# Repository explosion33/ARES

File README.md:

# ARES
Controls and Electronics Repository for SARP's Autonomous Recovery Experimental System (ARES).

## Directory / Ownership

[CC1200 Radio Board / ARES RF Board](https://github.com/stars/explosion33/lists/cc1200-radio-project) | Ethan Armstrong
<br/>
ARES RF board group: KiCad files, Firmware, supporting software

*/CAD*
<br/>
ARES PCB CAD

*/HBridgeTest*
<br/>
HBridge breadboard sample / control code

*/Hardware/Flight_Computer* | Jimmy Fowler
<br/>
ARES Flight Computer PCB Kicad Files

*/Hardware/motor_control_design* | Oliver Buehrer, Ethan Armstrong
<br/>
ARES Actuation (Motor Control) / Power Supply Board Kicad files

*/Renders*
<br/>
ARES PCB Renders

*/Software/Simulation* | Jimmy Fowler
<br/>
ARES simulation code

*/Testbed*
<br/>
ARES Testbed firmware

*/UI*
<br/>
ARES Ground Station UI

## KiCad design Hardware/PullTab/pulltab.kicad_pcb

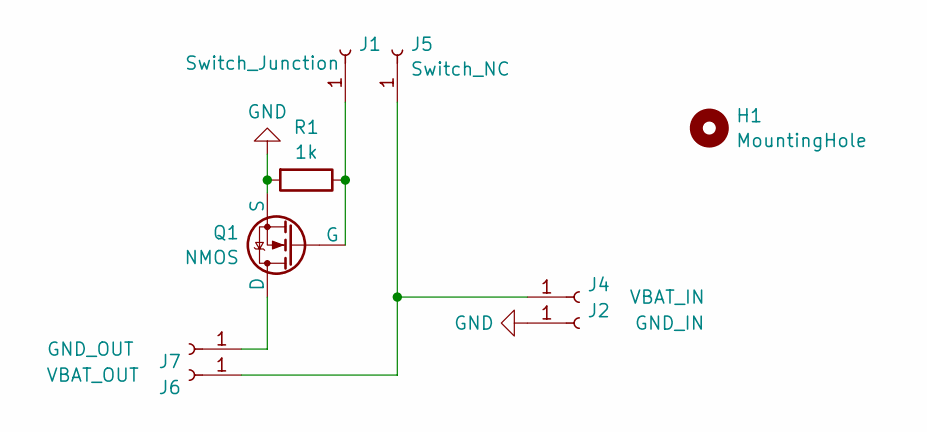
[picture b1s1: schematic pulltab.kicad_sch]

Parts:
H1: MountingHole; MountingHole_2.2mm_M2
J1: Switch_Junction; TestPoint_Pad_2.5x2.5mm
J2: GND_IN; TestPoint_Pad_4.0x4.0mm
J4: VBAT_IN; TestPoint_Pad_4.0x4.0mm
J5: Switch_NC; TestPoint_Pad_2.5x2.5mm
J6: VBAT_OUT; TestPoint_Pad_4.0x4.0mm
J7: GND_OUT; TestPoint_Pad_4.0x4.0mm
Q1: NMOS; TO-220-3_Horizontal_TabDown
R1: 1k; R_Axial_DIN0204_L3.6mm_D1.6mm_P5.08mm_Horizontal

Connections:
GND: J2.1, Q1.3 (S), R1.2
unnamed: J1.1, Q1.1 (G), R1.1
unnamed: J4.1, J5.1, J6.1
unnamed: J7.1, Q1.2 (D)

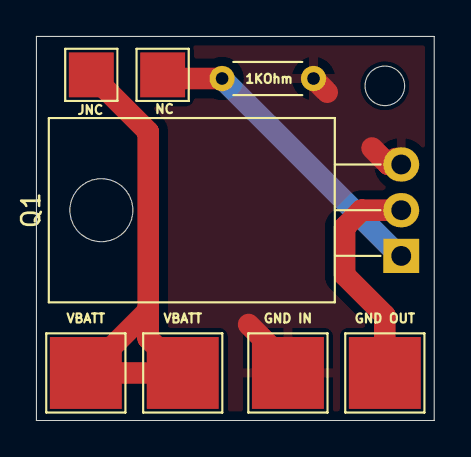
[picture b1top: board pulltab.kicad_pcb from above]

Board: 2 copper layers, 22.1 x 21.3 mm, 9 parts (0 on the bottom side), 4 nets.

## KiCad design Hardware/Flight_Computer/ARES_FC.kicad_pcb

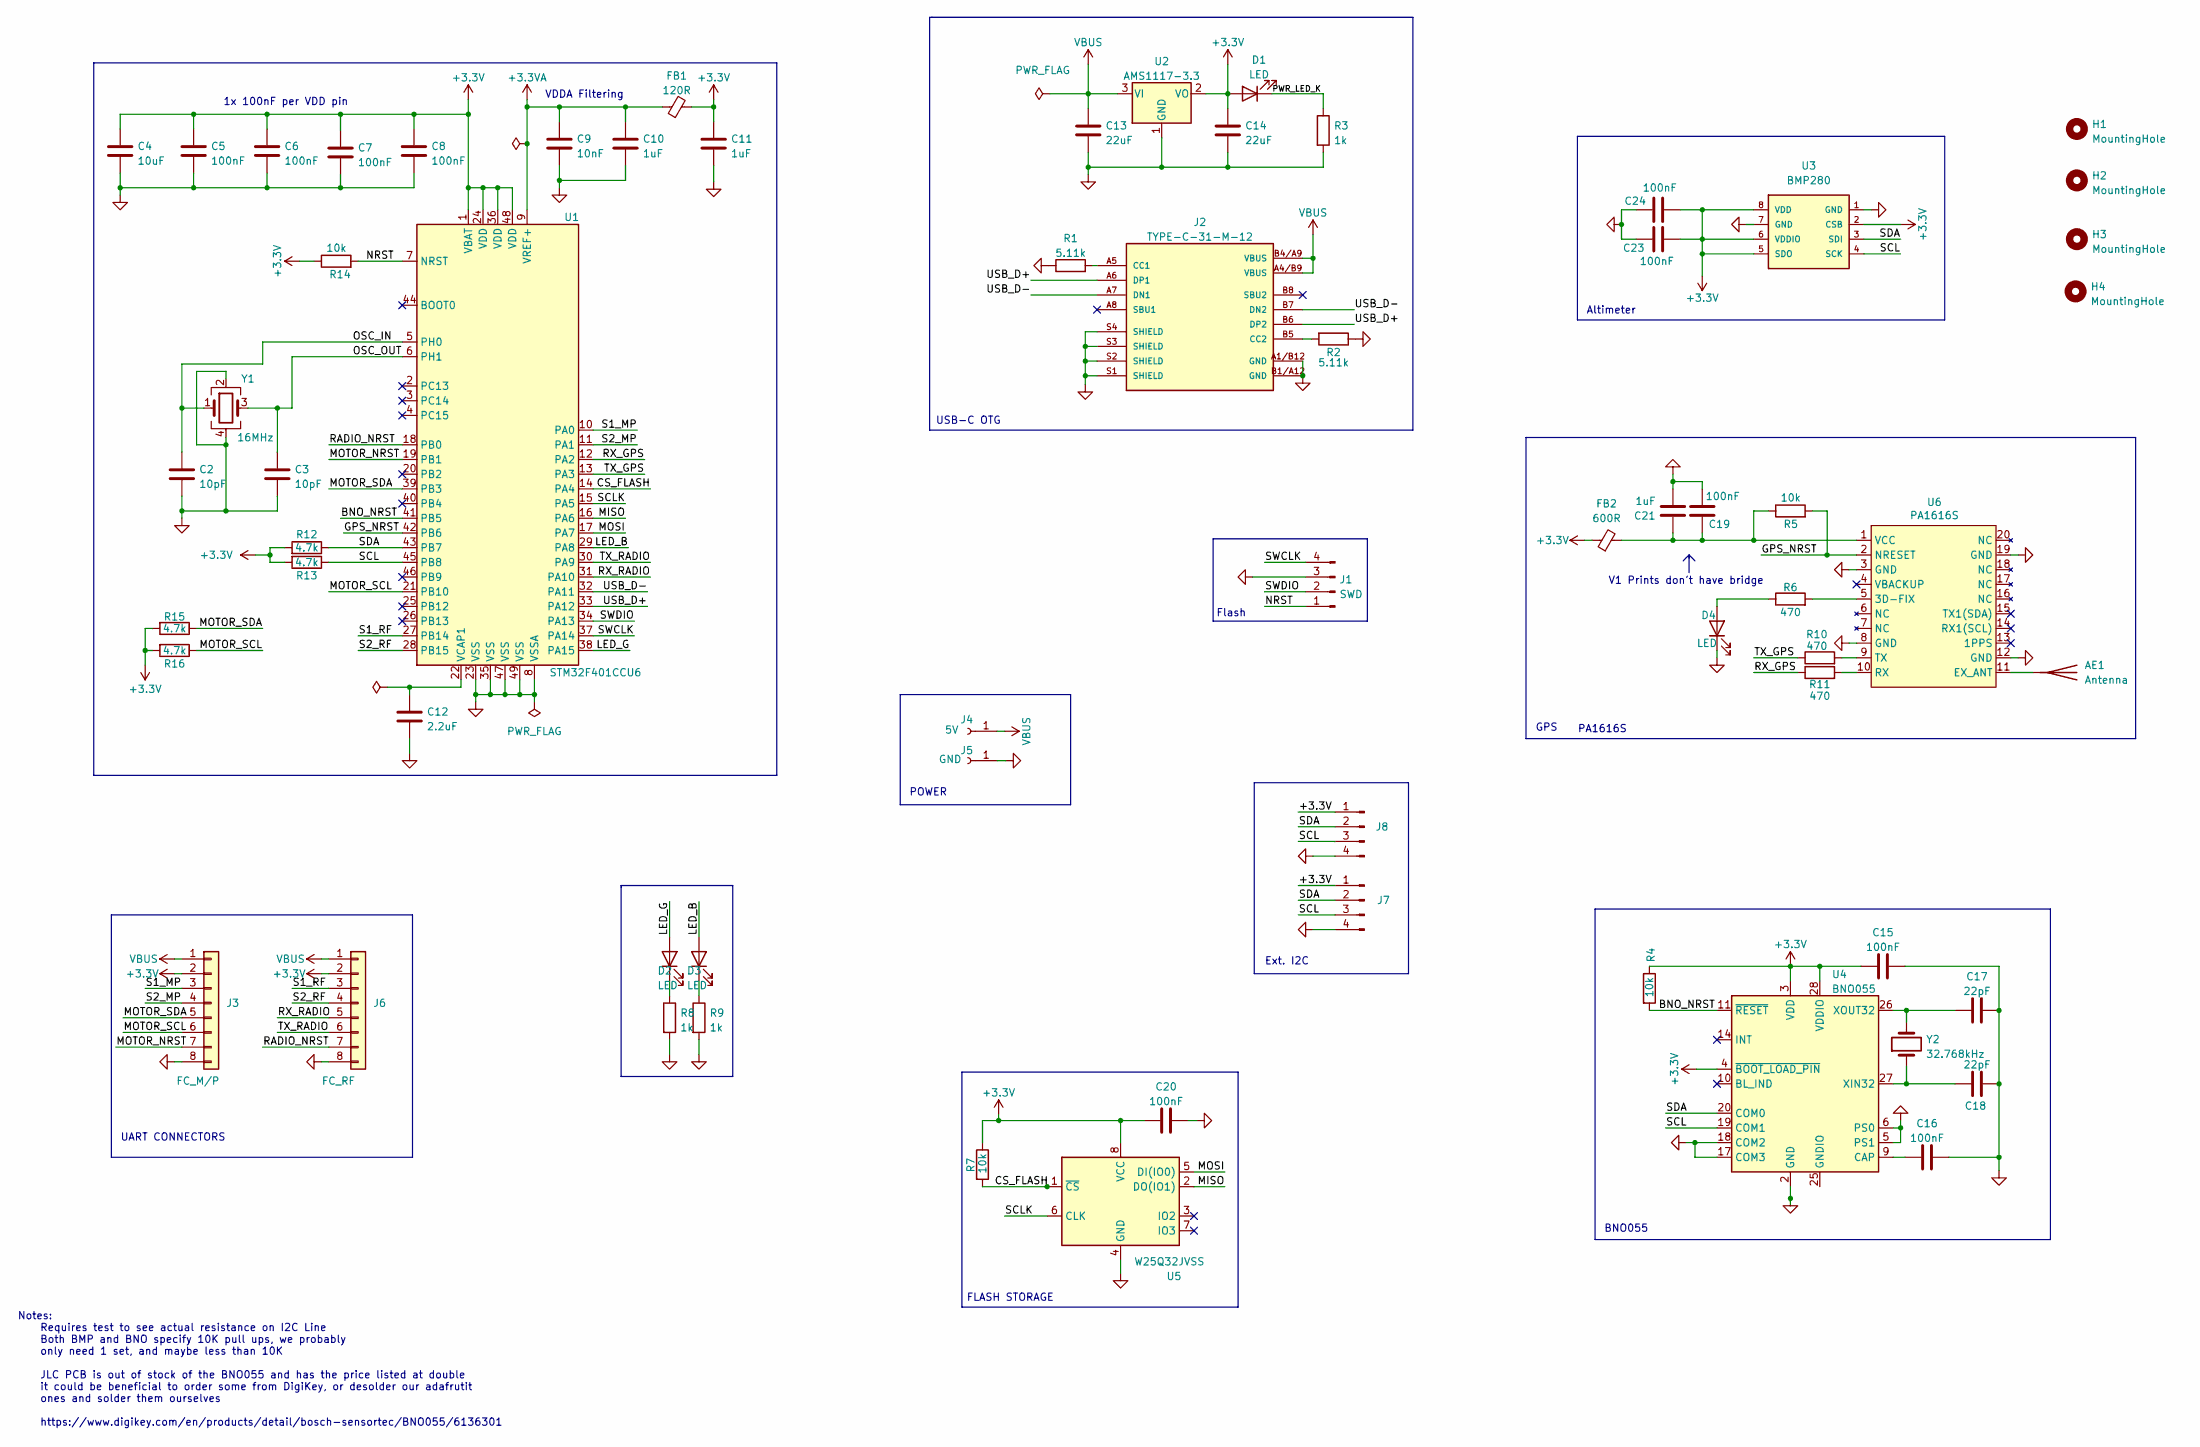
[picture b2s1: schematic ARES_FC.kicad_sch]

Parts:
AE1: Antenna; U.FL_Molex_MCRF_73412-0110_Vertical; LCSC Part C5137195
C2, C3: 10pF; C_0402_1005Metric; LCSC Part C32949
C4: 10uF; C_0603_1608Metric; LCSC Part C19702
C5, C6, C7, C8, C15, C16, C19, C20, C23, C24: 100nF; C_0402_1005Metric; LCSC Part C307331
C9: 10nF; C_0402_1005Metric; LCSC Part C15195
C10, C11, C21: 1uF; C_0402_1005Metric; LCSC Part C52923
C12: 2.2uF; C_0402_1005Metric; LCSC Part C12530
C13, C14: 22uF; C_0805_2012Metric; LCSC Part C5674
C17, C18: 22pF; C_0402_1005Metric; LCSC Part C466226
D1, D2: LED; LED_0603_1608Metric; LCSC Part C12624
D3: LED; LED_0603_1608Metric; LCSC Part C2288
D4: LED; LED_0603_1608Metric; LCSC Part C2290
FB1: 120R; L_0603_1608Metric; LCSC Part C85831
FB2: 600R; L_0603_1608Metric; LCSC Part C88976
H1, H2, H3, H4: MountingHole; MountingHole_2.2mm_M2
J1: SWD; PinHeader_1x04_P2.54mm_Vertical; LCSC Part C3025061
J2: TYPE-C-31-M-12; HRO_TYPE-C-31-M-12; PARTREV 2020.12.08; LCSC Part C165948
J3: FC_M/P; Molex_200528-0080_1x08-1MP_P1.00mm_Horizontal; LCSC Part C132510
J4: 5V; TestPoint_THTPad_2.5x2.5mm_Drill1.2mm
J5: GND; TestPoint_THTPad_2.5x2.5mm_Drill1.2mm
J6: FC_RF; Molex_200528-0080_1x08-1MP_P1.00mm_Horizontal; LCSC Part C132510
J7, J8: Conn_01x04_Pin; JST_SH_BM04B-SRSS-TB_1x04-1MP_P1.00mm_Vertical; LCSC Part C160390
R1, R2: 5.11k; R_0402_1005Metric; LCSC Part C25906
R3, R8, R9: 1k; R_0402_1005Metric; LCSC Part C11702
R4, R5, R7, R14: 10k; R_0402_1005Metric; LCSC Part C60490
R6, R10, R11: 470; R_0402_1005Metric; LCSC Part 0402WGJ0471TCE
R12, R13, R15, R16: 4.7k; R_0402_1005Metric; LCSC Part C119339
U1: STM32F401CCU6; QFN-48-1EP_7x7mm_P0.5mm_EP5.6x5.6mm; LCSC Part C79861
U2: AMS1117-3.3; SOT-223-3_TabPin2; LCSC Part C6186
U3: BMP280; XDCR_BMP280; PART_REV 1.19; LCSC Part C83291
U4: BNO055; LGA-28_5.2x3.8mm_P0.5mm; LCSC Part C93216
U5: W25Q32JVSS; SOIC-8_5.23x5.23mm_P1.27mm; LCSC Part C82344
U6: PA1616S; XCVR_CD-PA1616D; LCSC Part C9900146965
Y1: 16MHz; Crystal_SMD_3225-4Pin_3.2x2.5mm; LCSC Part C13738
Y2: 32.768kHz; Crystal_SMD_3215-2Pin_3.2x1.5mm; LCSC Part C32346

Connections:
+3.3V: C4.1, C5.1, C6.1, C7.1, C8.1, C11.1, C14.1, C15.1, C20.1, C23.2, C24.2, D1.2 (A), FB1.2, FB2.1, J3.2, J6.2, J7.1, J8.1, R4.1, R7.1, R12.2, R13.2, R14.1, R15.2, R16.2, U1.1 (VBAT), U1.24 (VDD), U1.36 (VDD), U1.48 (VDD), U2.2 (VO), U3.2 (CSB), U3.5 (SDO), U3.6 (VDDIO), U3.8 (VDD), U4.3 (VDD), U4.4 (~BOOT_LOAD_PIN), U4.28 (VDDIO), U5.8 (VCC)
+3.3VA: C9.1, C10.1, FB1.1, U1.9 (VREF+)
/BNO_NRST: R4.2, U1.41 (PB5), U4.11 (~RESET)
/CS_FLASH: R7.2, U1.14 (PA4), U5.1 (~CS)
/GPS_NRST: R5.2, U1.42 (PB6), U6.2 (NRESET)
/LED_B: D3.2 (A), U1.29 (PA8)
/LED_G: D2.2 (A), U1.38 (PA15)
/MISO: U1.16 (PA6), U5.2 (DO(IO1))
/MOSI: U1.17 (PA7), U5.5 (DI(IO0))
/MOTOR_NRST: J3.7, U1.19 (PB1)
/MOTOR_SCL: J3.6, R16.1, U1.21 (PB10)
/MOTOR_SDA: J3.5, R15.1, U1.39 (PB3)
/NRST: J1.1, R14.2, U1.7 (NRST); also elsewhere on the board
/OSC_IN: C2.1, U1.5 (PH0), Y1.1
/OSC_OUT: C3.1, U1.6 (PH1), Y1.3
/PWR_LED_K: D1.1 (K), R3.1
/RADIO_NRST: J6.7, U1.18 (PB0)
/RX_GPS: R11.1, U1.12 (PA2)
/RX_RADIO: J6.5, U1.31 (PA10)
/S1_MP: J3.3, U1.10 (PA0)
/S1_RF: J6.3, U1.27 (PB14)
/S2_MP: J3.4, U1.11 (PA1)
/S2_RF: J6.4, U1.28 (PB15)
/SCL: J7.3, J8.3, R13.1, U1.45 (PB8), U3.4 (SCK), U4.19 (COM1)
/SCLK: U1.15 (PA5), U5.6 (CLK)
/SDA: J7.2, J8.2, R12.1, U1.43 (PB7), U3.3 (SDI), U4.20 (COM0)
/SWCLK: J1.4, U1.37 (PA14)
/SWDIO: J1.2, U1.34 (PA13)
/TX_GPS: R10.1, U1.13 (PA3)
/TX_RADIO: J6.6, U1.30 (PA9)
/USB_D+: J2.A6 (DP1), J2.B6 (DP2), U1.33 (PA12)
/USB_D-: J2.A7 (DN1), J2.B7 (DN2), U1.32 (PA11)
GND: C2.2, C3.2, C4.2, C5.2, C6.2, C7.2, C8.2, C9.2, C10.2, C11.2, C12.2, C13.2, C14.2, C15.2, C16.2, C17.2, C18.2, C19.2, C20.2, C21.2, C23.1, C24.1, D4.1 (K), J1.3, J2.A1/B12 (GND), J2.B1/A12 (GND), J2.S1 (SHIELD), J2.S2 (SHIELD), J2.S3 (SHIELD), J2.S4 (SHIELD), J3.8, J5.1, J6.8, J7.4, J8.4, R1.1, R2.1, R3.2, R8.2, R9.2, U1.8 (VSSA), U1.23 (VSS), U1.35 (VSS), U1.47 (VSS), U1.49 (VSS), U2.1 (GND), U3.1 (GND), U3.7 (GND), U4.2 (GND), U4.5 (PS1), U4.6 (PS0), U4.17 (COM3), U4.18 (COM2), U5.4 (GND), U6.3 (GND), U6.8 (GND), U6.12 (GND), U6.19 (GND), Y1.2, Y1.4; also elsewhere on the board
unnamed: AE1.1 (A), U6.11 (EX_ANT)
unnamed: D2.1 (K), R8.1
unnamed: D3.1 (K), R9.1
unnamed: D4.2 (A), R6.1
unnamed: J2.A5 (CC1), R1.2
unnamed: J2.B5 (CC2), R2.2
unnamed: C12.1, U1.22 (VCAP1)
unnamed: C16.1, U4.9 (CAP)
unnamed: U4.15 (GNDIO), U4.16 (GNDIO), U4.25 (GNDIO)
unnamed: C18.1, U4.27 (XIN32), Y2.1
unnamed: C17.1, U4.26 (XOUT32), Y2.2
unnamed: R6.2, U6.5 (3D-FIX)
unnamed: R11.2, U6.10 (RX)
unnamed: R10.2, U6.9 (TX)
unnamed: C19.1, C21.1, FB2.2, R5.1, U6.1 (VCC)
VBUS: C13.1, J2.A4/B9 (VBUS), J2.B4/A9 (VBUS), J3.1, J4.1, J6.1, U2.3 (VI)

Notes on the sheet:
VDDA Filtering
Flash
Altimeter
FLASH STORAGE
PA1616S
V1 Prints don't have bridge
1x 100nF per VDD pin
Notes: Requires test to see actual resistance on I2C Line Both BMP and BNO specify 10K pull ups, we probably only need 1 set, and maybe less than 10K JLC PCB is out of stock of the BNO055 and has the price listed at double it could be beneficial to order some from DigiKey, or desolder our adafrutit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
USB-C OTG
GPS
UART CONNECTORS
BNO055
Ext. I2C
POWER

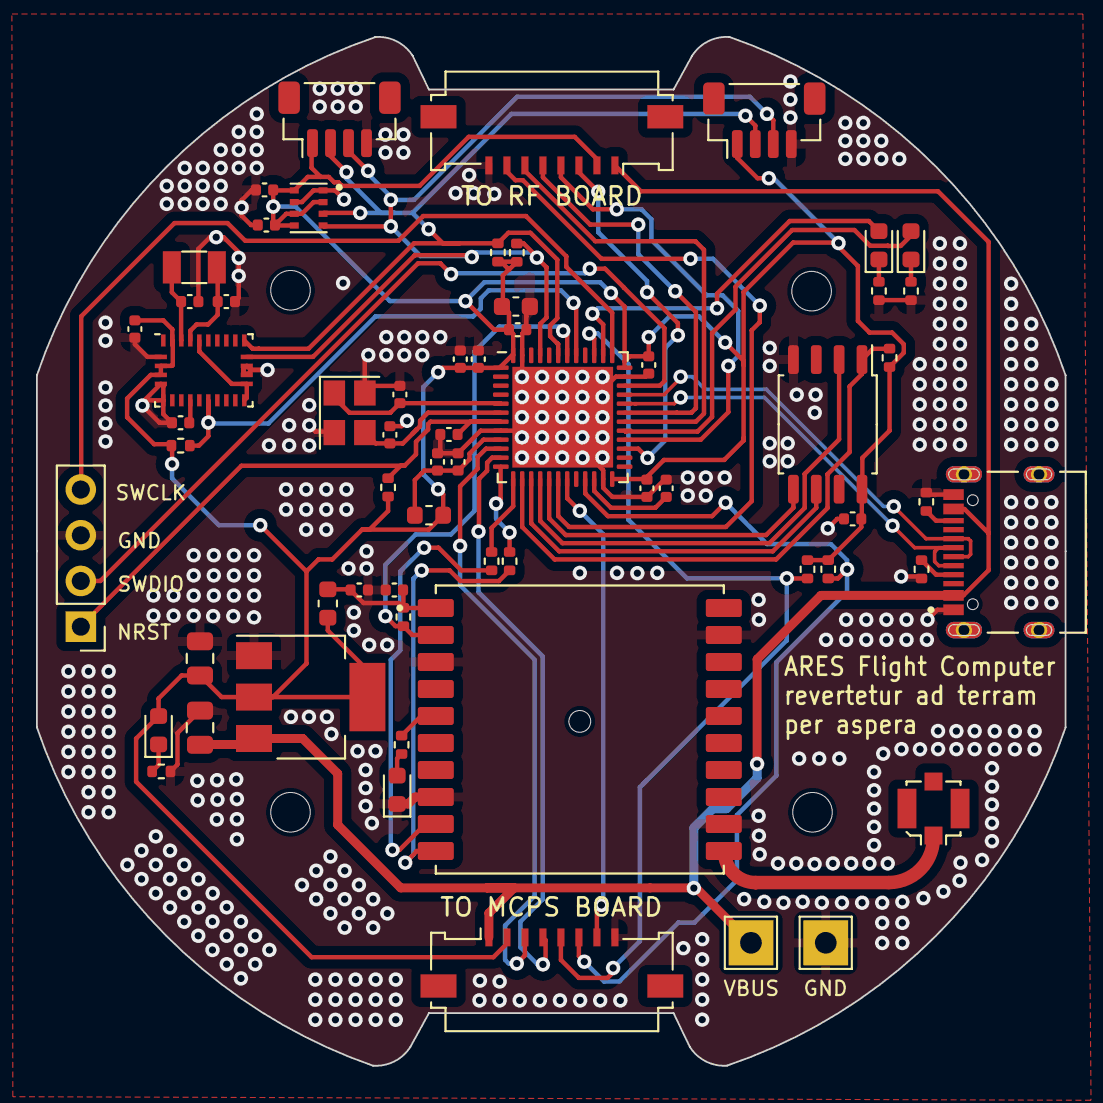
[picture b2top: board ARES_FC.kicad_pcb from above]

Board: 2 copper layers, 57.2 x 57.2 mm, 66 parts (0 on the bottom side), 49 nets.

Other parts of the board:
C1: 100nF; C_0402_1005Metric

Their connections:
/NRST: C1.1; also elsewhere on the board
GND: C1.2; also elsewhere on the board

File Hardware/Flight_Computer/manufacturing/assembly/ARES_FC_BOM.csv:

Comment,Designator,Footprint,LCSC Part,,
Antenna,AE1,Connector_Coaxial:U.FL_Molex_MCRF_73412-0110_Vertical,C5137195,,
1uF,"C10,C11,C21",Capacitor_SMD:C_0402_1005Metric,C52923,,
2.2uF,C12,Capacitor_SMD:C_0402_1005Metric,C12530,,
22uF,"C13,C14",Capacitor_SMD:C_0805_2012Metric,C5674,,
22pF,"C17,C18",Capacitor_SMD:C_0402_1005Metric,C466226,,
10pF,"C2,C3",Capacitor_SMD:C_0402_1005Metric,C32949,,
10uF,C4,Capacitor_SMD:C_0603_1608Metric,C19702,,
100nF,"C5,C6,C7,C8,C15,C16,C19,C20,C23,C24",Capacitor_SMD:C_0402_1005Metric,C307331,,
10nF,C9,Capacitor_SMD:C_0402_1005Metric,C15195,,
LED,"D1,D2",LED_SMD:LED_0603_1608Metric,C12624,,
LED,D3,LED_SMD:LED_0603_1608Metric,C2288,,
LED,D4,LED_SMD:LED_0603_1608Metric,C2290,,
120R,FB1,Inductor_SMD:L_0603_1608Metric,C85831,,
600R,FB2,Inductor_SMD:L_0603_1608Metric,C88976,,
MountingHole,"H1,H2,H3,H4",MountingHole:MountingHole_2.2mm_M2,,,
SWD,J1,Connector_PinHeader_2.54mm:PinHeader_1x04_P2.54mm_Vertical,,,
TYPE-C-31-M-12,J2,USBC:HRO_TYPE-C-31-M-12,C165948,,
FC_M/P,J3,Connector_FFC-FPC:Molex_200528-0080_1x08-1MP_P1.00mm_Horizontal,C132510,,
5V,J4,TestPoint:TestPoint_THTPad_2.5x2.5mm_Drill1.2mm,,,
GND,J5,TestPoint:TestPoint_THTPad_2.5x2.5mm_Drill1.2mm,,,
FC_RF,J6,Connector_FFC-FPC:Molex_200528-0080_1x08-1MP_P1.00mm_Horizontal,C132510,,
Conn_01x04_Pin,"J7,J8",Connector_JST:JST_SH_BM04B-SRSS-TB_1x04-1MP_P1.00mm_Vertical,C160390,,
5.11k,"R1,R2",Resistor_SMD:R_0402_1005Metric,C25906,,
4.7k,"R12,R13,R15,R16",Resistor_SMD:R_0402_1005Metric,C140158,,
1k,"R3,R8,R9",Resistor_SMD:R_0402_1005Metric,C11702,,
10k,"R4,R5,R7,R14",Resistor_SMD:R_0402_1005Metric,C60490,,
470,"R6,R10,R11",Resistor_SMD:R_0402_1005Metric,C25167,,
STM32F401CCU6,U1,Package_DFN_QFN:QFN-48-1EP_7x7mm_P0.5mm_EP5.6x5.6mm,C79861,,
AMS1117-3.3,U2,Package_TO_SOT_SMD:SOT-223-3_TabPin2,C6186,,
BMP280,U3,BMP280:XDCR_BMP280,C83291,,
BNO055,U4,Package_LGA:LGA-28_5.2x3.8mm_P0.5mm,C93216,,
W25Q32JVSS,U5,Package_SO:SOIC-8_5.23x5.23mm_P1.27mm,C82344,,
PA1616S,U6,CD-PA1616D:XCVR_CD-PA1616D,C9900146965,,
16MHz,Y1,Crystal:Crystal_SMD_3225-4Pin_3.2x2.5mm,C13738,,
32.768kHz,Y2,Crystal:Crystal_SMD_3215-2Pin_3.2x1.5mm, C32346,,

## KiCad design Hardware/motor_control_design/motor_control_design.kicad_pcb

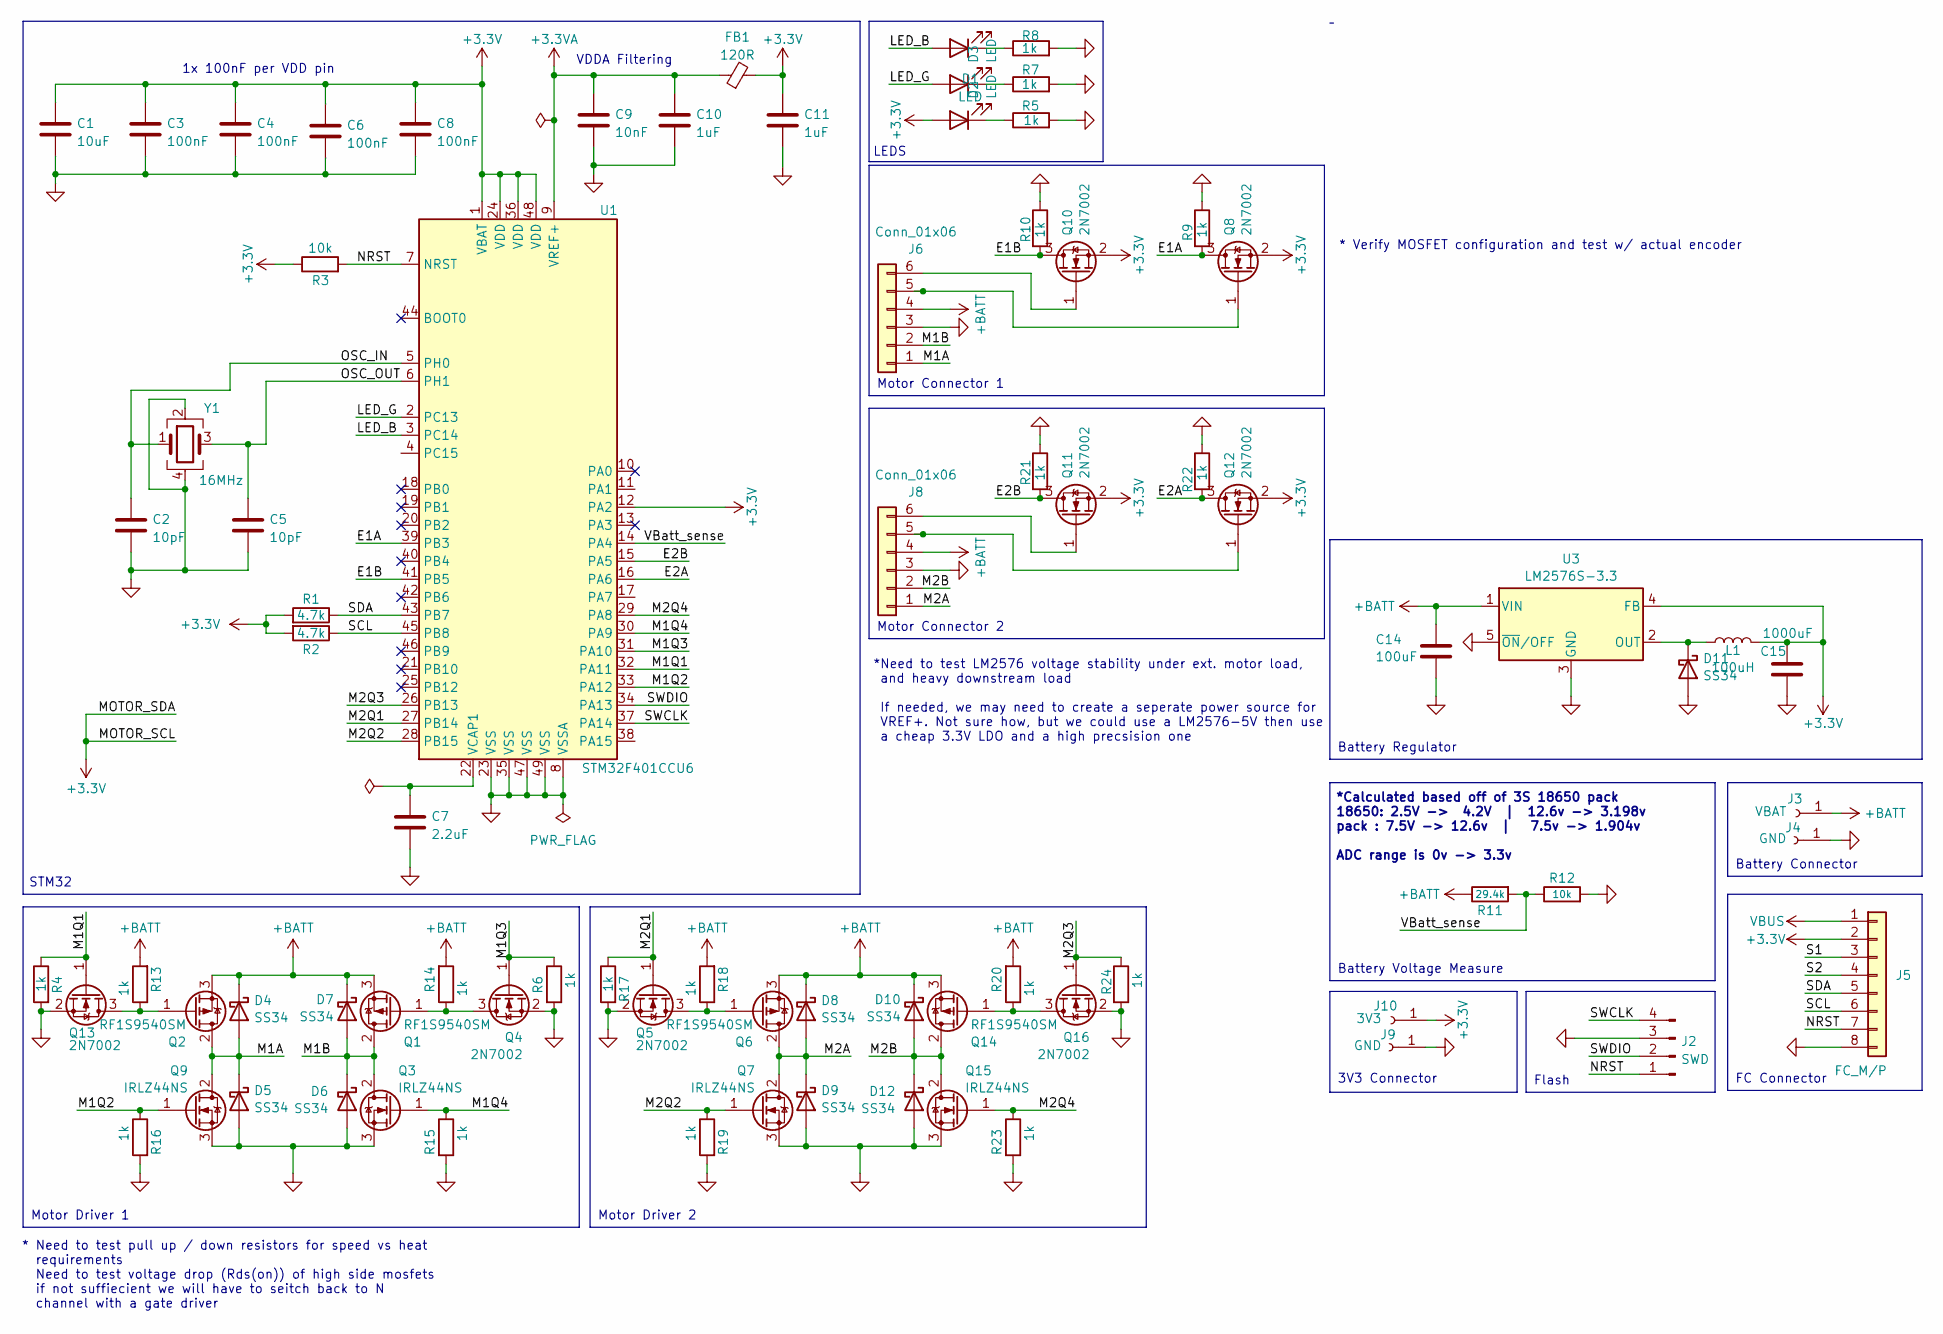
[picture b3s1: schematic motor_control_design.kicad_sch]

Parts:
C1: 10uF; C_0402_1005Metric; LCSC Part C19702
C2, C5: 10pF; C_0402_1005Metric; LCSC Part C32949
C3, C4, C6, C8: 100nF; C_0402_1005Metric; LCSC Part C307331
C7: 2.2uF; C_0402_1005Metric; LCSC Part C12530
C9: 10nF; C_0402_1005Metric; LCSC Part C15195
C10, C11: 1uF; C_0402_1005Metric; LCSC Part C52923
C14: 100uF; C_0805_2012Metric; LCSC Part C141660
C15: 1000uF; CP_Elec_10x10.5; LCSC Part C189257
D1: LED; LED_0603_1608Metric; LCSC Part C2286
D2: LED; LED_0603_1608Metric; LCSC Part C779453
D3: LED; LED_0603_1608Metric; LCSC Part C131286
D4, D5, D6, D7, D8, D9, D10, D11, D12: SS34; D_SMA; LCSC Part C3032484
FB1: 120R; L_0603_1608Metric; LCSC Part C85831
J2: SWD; PinHeader_1x04_P2.54mm_Vertical
J3: VBAT; TestPoint_THTPad_4.0x4.0mm_Drill2.0mm
J4, J9: GND; TestPoint_THTPad_4.0x4.0mm_Drill2.0mm
J5: FC_M/P; Molex_200528-0080_1x08-1MP_P1.00mm_Horizontal; LCSC Part C132510
J6, J8: Conn_01x06; CONN_S6B-XH-SM4-TB_JST
J10: 3V3; TestPoint_THTPad_4.0x4.0mm_Drill2.0mm
L1: 100uH; L_TaiTech_TMPC1265_13.5x12.5mm; LCSC Part C408533
Q1, Q2, Q6, Q14: RF1S9540SM; TO-263-2; LCSC Part C33903
Q3, Q7, Q9, Q15: IRLZ44NS; TO-263-2; LCSC Part C538199
Q4, Q5, Q8, Q10, Q11, Q12, Q13, Q16: 2N7002; SOT-23; LCSC Part C466660
R1, R2: 4.7k; R_0402_1005Metric; LCSC Part C174364
R3, R12: 10k; R_0402_1005Metric; LCSC Part C176114
R4, R5, R6, R7, R8, R9, R10, R13, R14, R15, R16, R17, R18, R19, R20, R21, R22, R23, R24: 1k; R_0402_1005Metric; LCSC Part C102758
R11: 29.4k; R_0402_1005Metric; LCSC Part C162880
U1: STM32F401CCU6; QFN-48-1EP_7x7mm_P0.5mm_EP5.6x5.6mm; LCSC Part C79861
U3: LM2576S-3.3; TO-263-5_TabPin3; LCSC Part C347412
Y1: 16MHz; Crystal_SMD_3225-4Pin_3.2x2.5mm; LCSC Part C13738

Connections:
+3.3V: C1.1, C3.1, C4.1, C6.1, C8.1, C11.1, C15.2, D1.2 (A), FB1.2, J5.2, J10.1, L1.2, Q8.2 (S), Q10.2 (S), Q11.2 (S), Q12.2 (S), R1.2, R2.2, R3.1, U1.1 (VBAT), U1.12 (PA2), U1.24 (VDD), U1.36 (VDD), U1.48 (VDD), U3.4 (FB)
+3.3VA: C9.1, C10.1, FB1.1, U1.9 (VREF+)
+BATT: C14.2, D4.1 (K), D7.1 (K), D8.1 (K), D10.1 (K), J3.1, J6.4, J8.4, Q1.3 (S), Q2.3 (S), Q6.3 (S), Q14.3 (S), R11.1, R13.2, R14.2, R18.2, R20.2, U3.1 (VIN)
/E1A: Q8.3 (D), R9.2, U1.39 (PB3)
/E1B: Q10.3 (D), R10.2, U1.41 (PB5)
/E2A: Q12.3 (D), R22.2, U1.16 (PA6)
/E2B: Q11.3 (D), R21.2, U1.15 (PA5)
/LED_B: D3.2 (A), U1.3 (PC14)
/LED_G: D2.2 (A), U1.2 (PC13)
/M1A: D4.2 (A), D5.1 (K), J6.1, Q2.2 (D), Q9.2 (D)
/M1B: D6.1 (K), D7.2 (A), J6.2, Q1.2 (D), Q3.2 (D)
/M1Q1: Q13.1 (G), R4.1, U1.32 (PA11)
/M1Q2: Q9.1 (G), R16.1, U1.33 (PA12)
/M1Q3: Q4.1 (G), R6.1, U1.31 (PA10)
/M1Q4: Q3.1 (G), R15.1, U1.30 (PA9)
/M2A: D8.2 (A), D9.1 (K), J8.1, Q6.2 (D), Q7.2 (D)
/M2B: D10.2 (A), D12.1 (K), J8.2, Q14.2 (D), Q15.2 (D)
/M2Q1: Q5.1 (G), R17.1, U1.27 (PB14)
/M2Q2: Q7.1 (G), R19.1, U1.28 (PB15)
/M2Q3: Q16.1 (G), R24.1, U1.26 (PB13)
/M2Q4: Q15.1 (G), R23.1, U1.29 (PA8)
/NRST: J2.1, J5.7, R3.2, U1.7 (NRST)
/OSC_IN: C2.1, U1.5 (PH0), Y1.1
/OSC_OUT: C5.1, U1.6 (PH1), Y1.3
/S1: J5.3
/S2: J5.4
/SCL: J5.6, R2.1, U1.45 (PB8)
/SDA: J5.5, R1.1, U1.43 (PB7)
/SWCLK: J2.4, U1.37 (PA14)
/SWDIO: J2.2, U1.34 (PA13)
/VBatt_sense: R11.2, R12.1, U1.14 (PA4)
GND: C1.2, C2.2, C3.2, C4.2, C5.2, C6.2, C7.2, C8.2, C9.2, C10.2, C11.2, C14.1, C15.1, D5.2 (A), D6.2 (A), D9.2 (A), D11.2 (A), D12.2 (A), J2.3, J4.1, J5.8, J6.3, J8.3, J9.1, Q3.3 (S), Q4.2 (S), Q5.2 (S), Q7.3 (S), Q9.3 (S), Q13.2 (S), Q15.3 (S), Q16.2 (S), R4.2, R5.2, R6.2, R7.2, R8.2, R9.1, R10.1, R12.2, R15.2, R16.2, R17.2, R19.2, R21.1, R22.1, R23.2, R24.2, U1.8 (VSSA), U1.23 (VSS), U1.35 (VSS), U1.47 (VSS), U1.49 (VSS), U3.3 (GND), U3.5 (~ON/OFF), Y1.2, Y1.4
unnamed: D1.1 (K), R5.1
unnamed: D2.1 (K), R7.1
unnamed: D3.1 (K), R8.1
unnamed: D11.1 (K), L1.1, U3.2 (OUT)
unnamed: J6.5, Q8.1 (G)
unnamed: J6.6, Q10.1 (G)
unnamed: J8.5, Q12.1 (G)
unnamed: J8.6, Q11.1 (G)
unnamed: Q1.1 (G), Q4.3 (D), R14.1
unnamed: Q5.3 (D), Q6.1 (G), R18.1
unnamed: Q2.1 (G), Q13.3 (D), R13.1
unnamed: Q14.1 (G), Q16.3 (D), R20.1
unnamed: C7.1, U1.22 (VCAP1)
VBUS: J5.1

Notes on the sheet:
Battery Regulator
Motor Driver 1
* Verify MOSFET configuration and test w/ actual encoder
Motor Connector 1
* Need to test pull up / down resistors for speed vs heat requirements Need to test voltage drop (Rds(on)) of high side mosfets if not suffiecient we will have to seitch back to N channel with a gate driver
*Calculated based off of 3S 18650 pack 18650: 2.5V -> 4.2V | 12.6v -> 3.198v pack : 7.5V -> 12.6v | 7.5v -> 1.904v ADC range is 0v -> 3.3v
Motor Connector 2
Motor Driver 2
*Need to test LM2576 voltage stability under ext. motor load, and heavy downstream load If needed, we may need to create a seperate power source for VREF+. Not sure how, but we could use a LM2576-5V then use a cheap 3.3V LDO and a high precsision one
Battery Connector
Battery Voltage Measure
VDDA Filtering
Flash
1x 100nF per VDD pin
FC Connector
3V3 Connector
LEDS
STM32

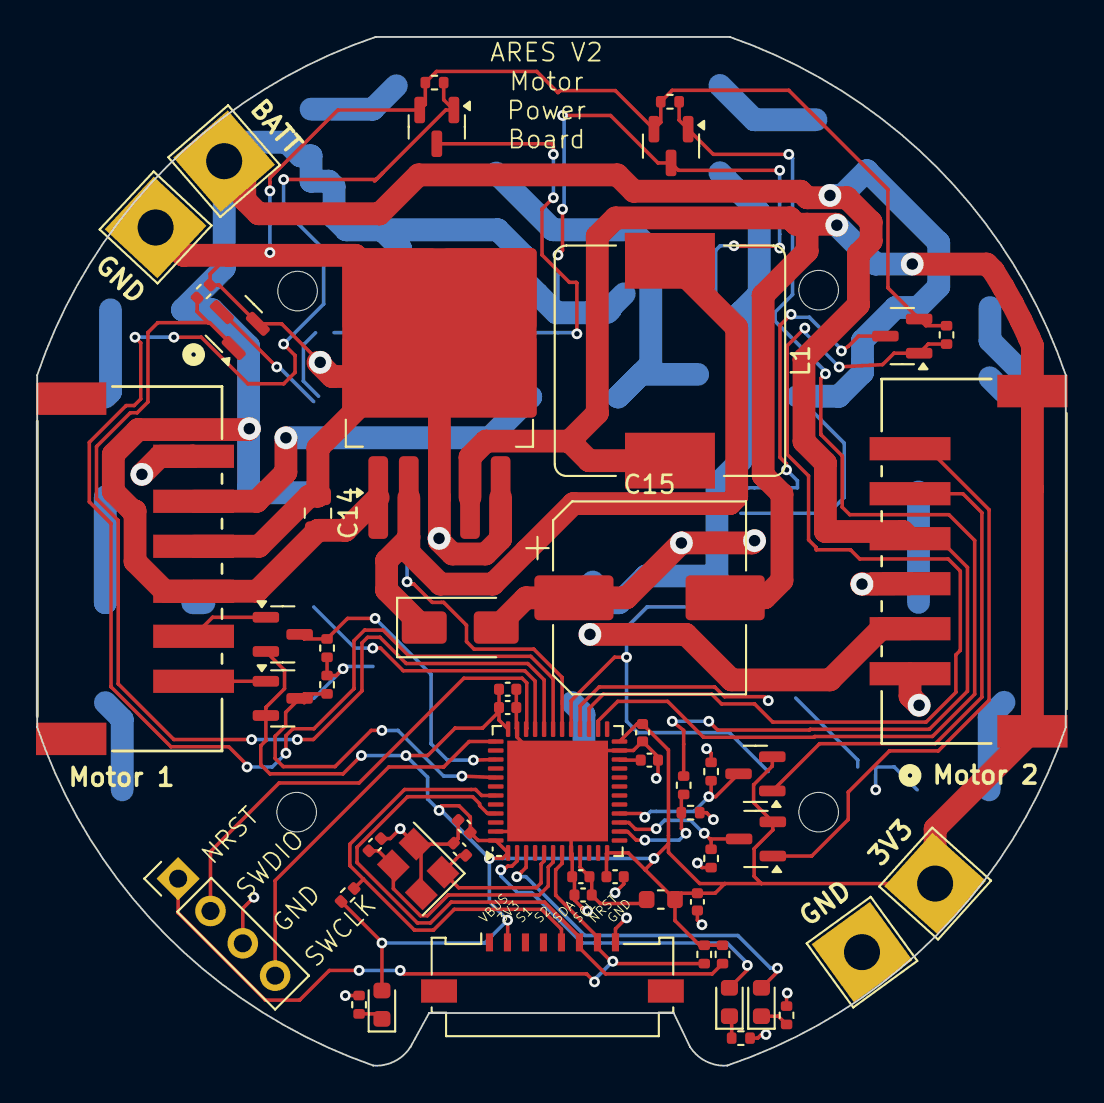
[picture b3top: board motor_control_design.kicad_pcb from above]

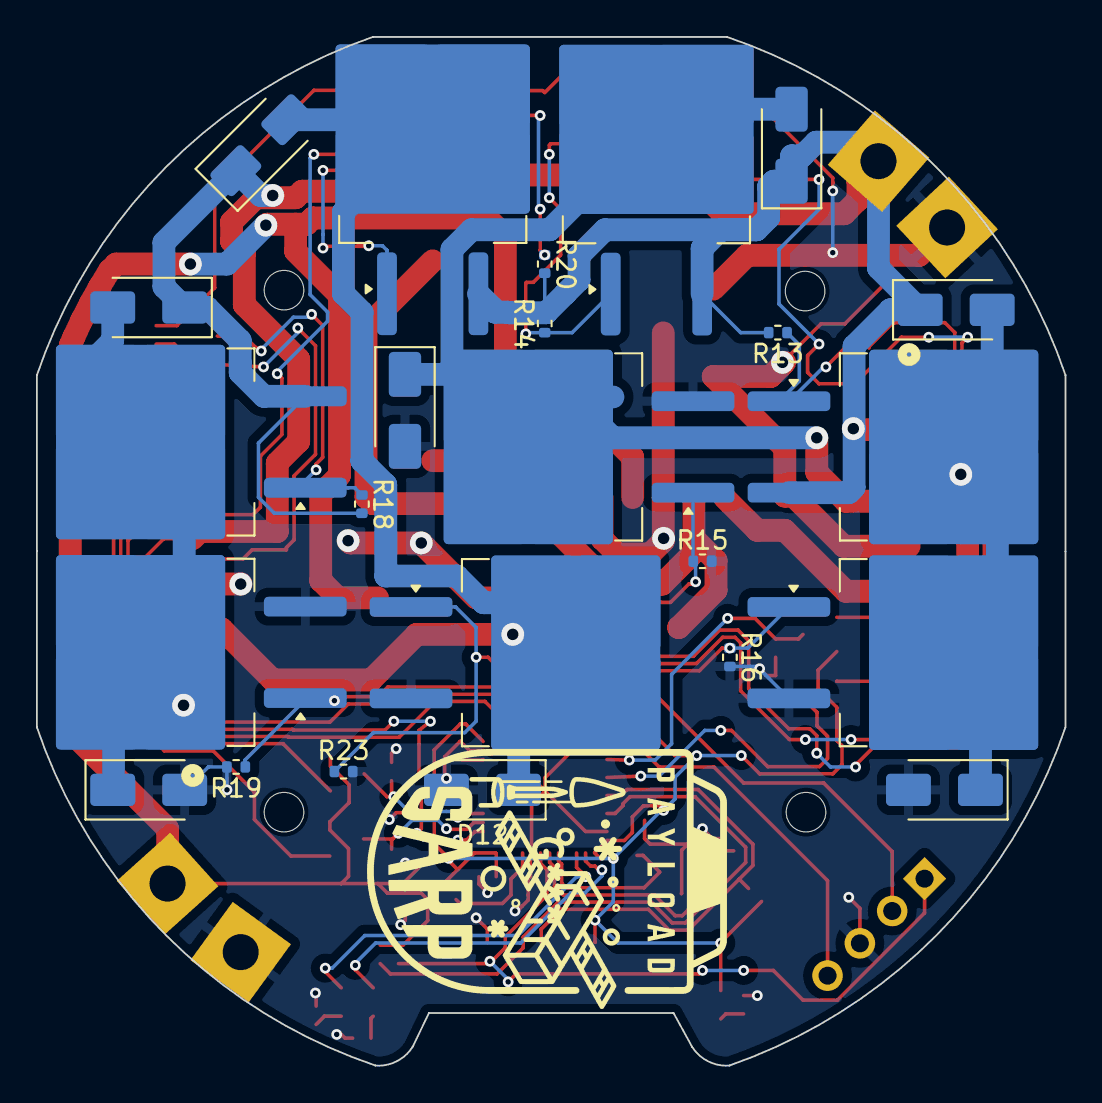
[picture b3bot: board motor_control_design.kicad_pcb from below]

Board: 2 copper layers, 57.1 x 57.2 mm, 78 parts (24 on the bottom side), 43 nets.

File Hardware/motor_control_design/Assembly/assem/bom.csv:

Comment,Designator,Footprint,LCSC Part #
10uF Unpolarized capacitor,C1,C_0402_1005Metric,C19702
10pF Unpolarized capacitor,"C2,C5",C_0402_1005Metric,C32949
100nF Unpolarized capacitor,"C3,C4,C6,C8",C_0402_1005Metric,C307331
2.2uF Unpolarized capacitor,C7,C_0402_1005Metric,C12530
10nF Unpolarized capacitor,C9,C_0402_1005Metric,C15195
1uF Unpolarized capacitor,"C10,C11",C_0402_1005Metric,C52923
100uF Unpolarized capacitor,C14,C_0805_2012Metric,C141660
330uF Unpolarized capacitor,C15,C_0402_1005Metric,C19702
LED Light emitting diode,"D1,D2,D3",LED_0603_1608Metric,C273598
"SS34 40V 3A Schottky Diode, SMA","D4,D5,D6,D7,D8,D9,D10,D11,D12",D_SMA,C3032484
"120R Ferrite bead, small symbol",FB1,L_0603_1608Metric,C85831
"SWD Generic connector, single row, 01x04, script generated (kicad-library-utils/schlib/autogen/connector/)",J2,PinHeader_1x04_P2.54mm_Vertical,
"VBAT Generic connector, single row, 01x01, script generated (kicad-library-utils/schlib/autogen/connector/)",J3,TestPoint_THTPad_4.0x4.0mm_Drill2.0mm,
"GND Generic connector, single row, 01x01, script generated (kicad-library-utils/schlib/autogen/connector/)","J4,J9",TestPoint_THTPad_4.0x4.0mm_Drill2.0mm,
"FC_M/P Generic connector, single row, 01x08, script generated (kicad-library-utils/schlib/autogen/connector/)",J5,Molex_200528-0080_1x08-1MP_P1.00mm_Horizontal,C124378
"Conn_01x06 Generic connector, single row, 01x06, script generated (kicad-library-utils/schlib/autogen/connector/)","J6,J8",CONN_S6B-XH-SM4-TB_JST,
"3V3 Generic connector, single row, 01x01, script generated (kicad-library-utils/schlib/autogen/connector/)",J10,TestPoint_THTPad_4.0x4.0mm_Drill2.0mm,
100uH Inductor,L1,L_12x12mm_H4.5mm,C7431084
"RF1S9540SM -74A Id, -55V Vds, Single P-Channel HEXFET Power MOSFET, 20mOhm Ron, TO-220AB","Q1,Q2,Q6,Q14",TO-263-2, C33903
"IRLZ44NS 47A Id, 55V Vds, 22mOhm Rds Single N-Channel HEXFET Power MOSFET, TO-220AB","Q3,Q7,Q9,Q15",TO-263-2, C538199
"2N7002 0.115A Id, 60V Vds, N-Channel MOSFET, SOT-23","Q4,Q5,Q8,Q10,Q11,Q12,Q13,Q16",SOT-23,C466660
4.7k Resistor,"R1,R2",R_0402_1005Metric,C174364
10k Resistor,"R3,R12",R_0402_1005Metric,C176114
1k Resistor,"R4,R5,R6,R7,R8,R9,R10,R13,R14,R15,R16,R17,R18,R19,R20,R21,R22,R23,R24",R_0402_1005Metric,C102758
29.4k Resistor,R11,R_0402_1005Metric,C162880
"STM32F401CCU6 ARM Cortex-M4 MCU, 256KB flash, 64KB RAM, 84MHz, 1.7-3.6V, 36 GPIO, UFQFPN-48",U1,QFN-48-1EP_7x7mm_P0.5mm_EP5.6x5.6mm,C79861
"LM2576S-3.3 3.3V, 3A SIMPLE SWITCHER® Step-Down Voltage Regulator, TO-263",U3,TO-263-5_TabPin3,C347414
"16MHz Four pin crystal, GND on pins 2 and 4",Y1,Crystal_SMD_3225-4Pin_3.2x2.5mm,C13738

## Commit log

2024-08-08 initial commit
    Added folders for hardware and software and copied over RCS board (sarprcs repo).
2024-08-14 Added RCS Testbed blink code
2024-08-14 removed RCS-specific components
    removed solenoid connectors, SPI connectors, LTC, and extra IMU
2024-08-14 added usb output
2024-08-18 Added GPS and Altimeter to schematic
    still need to add wires
2024-08-18 changed filenames to ARES_FC (Flight Computer)
2024-08-20 added PA1616D Symbol
2024-08-20 started filling out GPS schematic
2024-08-21 finished GPS schematic
2024-08-27 finished schematic for MBP280, GPS and UARTs
2024-08-27 Fixed "RCS Board Problems"
    in RCS Board Problems Discord Thread.
2024-09-04 created kicad project for motor control board
2024-09-06 first pass FC changes
2024-09-06 Seperated lines that were previously merged All UART devices were on the same bus and have since been moved to GPS_UART and RADIO_UART Motor UART has been replaced with I2C NRST lines have been seper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
2024-09-06 Converted BMP280 to I2C was wrongly setup as SPI
2024-09-06 forgot to save everything before last commit
2024-09-06 added edges and screw hole layout for 60mm board
2024-09-11 Routing 75% complete
    added all footprints and connected most components
2024-09-12 Fixed PCB Edge
2024-09-12 routing 99% done
    double check external antenna connector. S1 & S2 unused for ribbons. DRC not completed.
2024-09-12 DRC fixes
2024-09-12 Antenna and Model Changes Added Fencing Vias to Ext. GPS Antenna Added 3D Models for Ribbon Connectors and GPS
2024-09-15 Motor Control Base Setup Copied Base STM32 schema from Flight Computer Project Copied and Modified Edge Cuts from Flight Computer Added LM2576 Schematic
2024-09-15 Added Vbat Sensing schema to motor board
2024-09-15 fixed ribbon connectors and S1 & S2
2024-09-16 Start of the hbridge test code
2024-09-16 tiny routing change for aesthetic purposes
2024-09-16 Added both H-Bridge schemas (pending testing)
2024-09-17 Finished motor controller schematic and routing
2024-09-18 Updated Motor control schema and routing to match new hbridge design
2024-09-18 Moved Hbridge code to testbed since I fried all my other mcus and had to use RCS
2024-09-18 added motor board renders
2024-09-18 Cleaned up motor board schema
2024-09-20 Uploaded CAD for all 3 boards
2024-09-20 Motor Board: Added LCSC Part Numbers Fixed missing ground on diode
2024-09-29 added most part numbers
2024-09-30 Motor Board: Optimized LM2576 circuit - bigger capacitor - better inductor Added assembly files (outdated)
2024-10-01 added U.FL part number
2024-10-01 added tentative external i2c connectors
2024-10-02 fixed motor conn. i2c and external i2c conn.s, changed PNs, added models
    new PN for Y2, added 3D models for BMP, Antenna, and ext. i2c connectors.
2024-10-11 added BOMs
2024-10-24 Start of UI sub directory
2024-11-07 initializing simulation
2024-11-07 Added Via Stiching and ViPs to Motor Board
2024-11-07 Added Fencing Vias and ViPs to FC
2024-11-07 Removed front copper traced under GPS Increased GPS feed line width to be 50ohm Curved GPS feed line to reduce emmisions
2024-11-08 Updated CAD and added Renders
2024-11-09 Initialize H3DOF sim
2024-11-11 aesthetic edits (silkscreen, etc.)
2024-11-11 connected GPS_NRST to STM32
2024-11-11 some LCSC Part (BOM) changes; more needed.
2024-11-12 changed C4 to 0603; removed vias on pads; added stitching vias
2024-11-13 fixed JLC part numbers and ran DRC
2024-11-13 some DRC warnings fixed
2024-11-13 Added more stitching vias to cutoff segments of ground plane Shrunk ViPs from 0.6/0.3 to 0.4/0.2
2024-11-13 hid silkscreen component labels
2024-11-14 initialize data analysis folder
2024-11-15 more PR data analysis
2024-11-16 lowkey I don't remember what changes I made
2024-11-21 added missing 3.3V bridge connection to GPS PS pin
2024-11-29 added gsim testing folder and did some sim stuff
2024-11-29 plot input break and output ang. velocity
2024-12-06 edited some plots on Monte Carlo w/ no ARES
2024-12-06 changed wording on some comments
2024-12-07 initialize FC and MCPS software folder
2024-12-13 lowkey forgor ... I think assembly files for motor board
2024-12-14 MCP_Testing codebase initial commit target configuration base led and motor1 simple control code
2025-01-11 PullTab PCB schematic, layout, gerbers, and prints
2025-01-11 added gbr svgs and lightburn project file
2025-01-14 sim edits
2025-01-18 fixed pulltab mosfet pin orientation added cad
2025-01-18 blackpill setup
2025-01-18 tf changes
2025-01-21 setup blackpill target again
2025-01-22 Added SYS_ID.mlx
    Completed First-draft System Identification for ARES horizontal input/output model.
2025-01-27 added TF from system ID to dynamics.m
2025-01-27 kappa_w = 0.2
2025-01-28 Corrected TF and closed simulink ctrl loop
    added zero to TF and started tuning PID in system_tf.slx
2025-02-07 initializing GPS drivers
2025-02-08 Implemented starting point for GPS Driver Fixed missing file issues in blackpill build target Added EUSBSerial class for better USBSerial support Updated main.cpp with working examples
2025-02-12 Initialized GPS.cpp and .h. Made structs and getMsgType function.
2025-02-18 initialized gpsReader.py
2025-02-19 Added class definition and initial methods to GPS.h
    added struct gpsState, enum NMEA_Type, GPS class def with methods getState(), getMsgType(), and update().
2025-02-19 implemented GPS.cpp to match revised header file
2025-02-19 moved state updates inside if-statement check
2025-02-19 changed integers in case() statements to NMEA_Types
2025-02-19 removed erroneous stuff at the bottom of GPS.cpp
2025-02-19 moved state variable initialization inside loop
2025-02-19 started rewriting main for test
2025-02-19 added float formatting w/ target_override
2025-02-25 getMsgType test works in main.cpp
2025-02-25 added getPosLTP function (not tested)
2025-02-26 can print message to port, debugging update() function
2025-02-27 tested artificial GGA message (it works)
2025-02-28 Added ollie_motor_control
2025-03-04 random simulation stuff
2025-03-04 testing latitude to radians function
2025-03-04 Initialized lat2rad.cpp
2025-03-04 added example GPS messsages with fix
2025-03-05 Initialization
2025-03-06 ported bootloader from ssl
2025-03-06 motor control PID
    Created motor controller pid class and created an example in main
2025-03-06 Added ARES bootloader config to MCP_testing Coppied Flasher software from ssl
2025-03-06 removed flasher cause it broke git
2025-03-06 moved FC Hardware files to own branch
2025-03-06 moved MCP Hardware to seperate branch
2025-03-07 Now reads data
2025-03-07 Updated with temperature conversion (error)
2025-03-08 Worked on Pressure/Temp readings
